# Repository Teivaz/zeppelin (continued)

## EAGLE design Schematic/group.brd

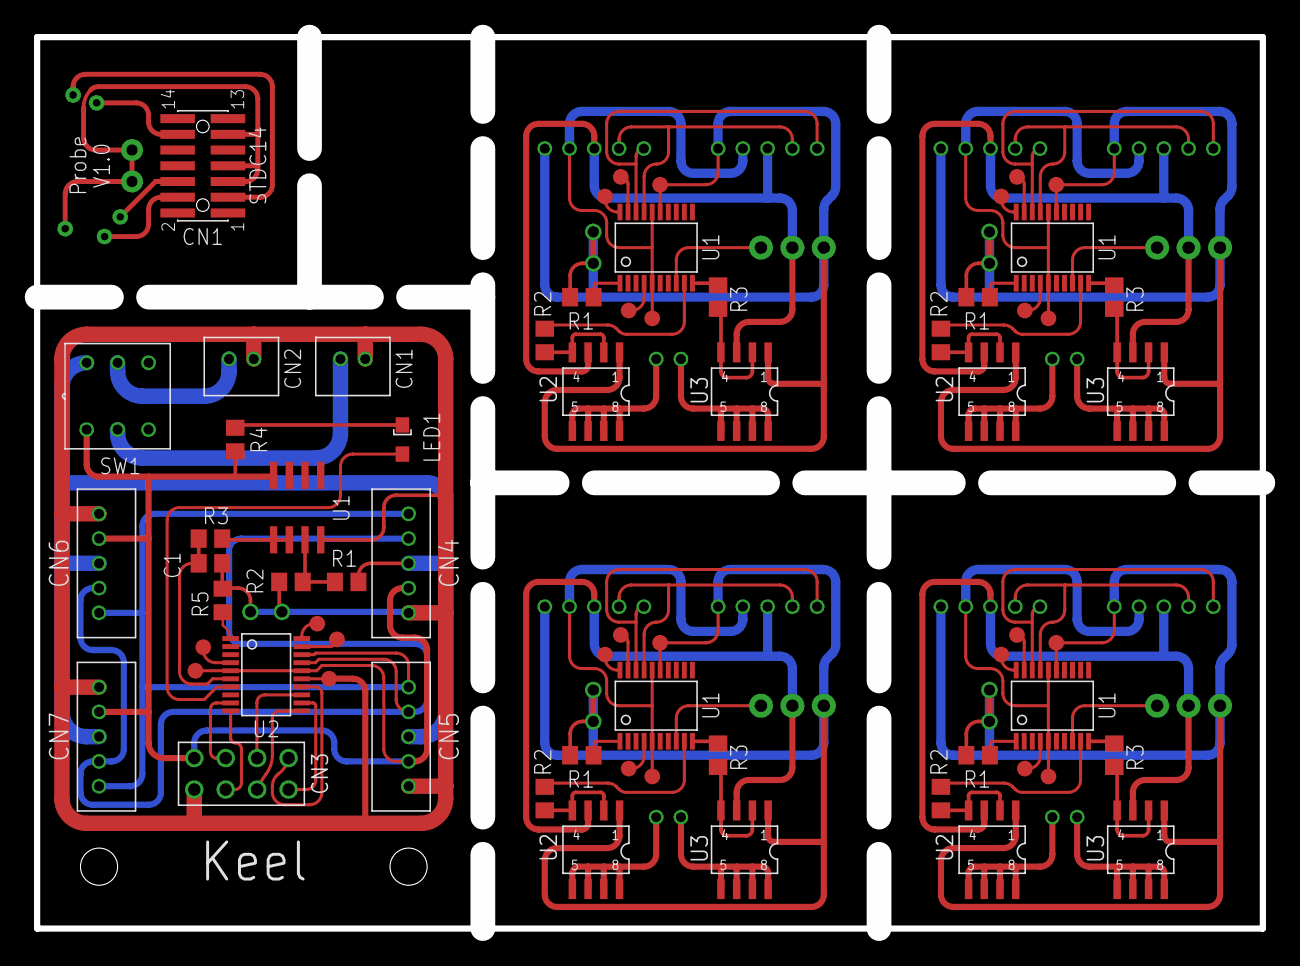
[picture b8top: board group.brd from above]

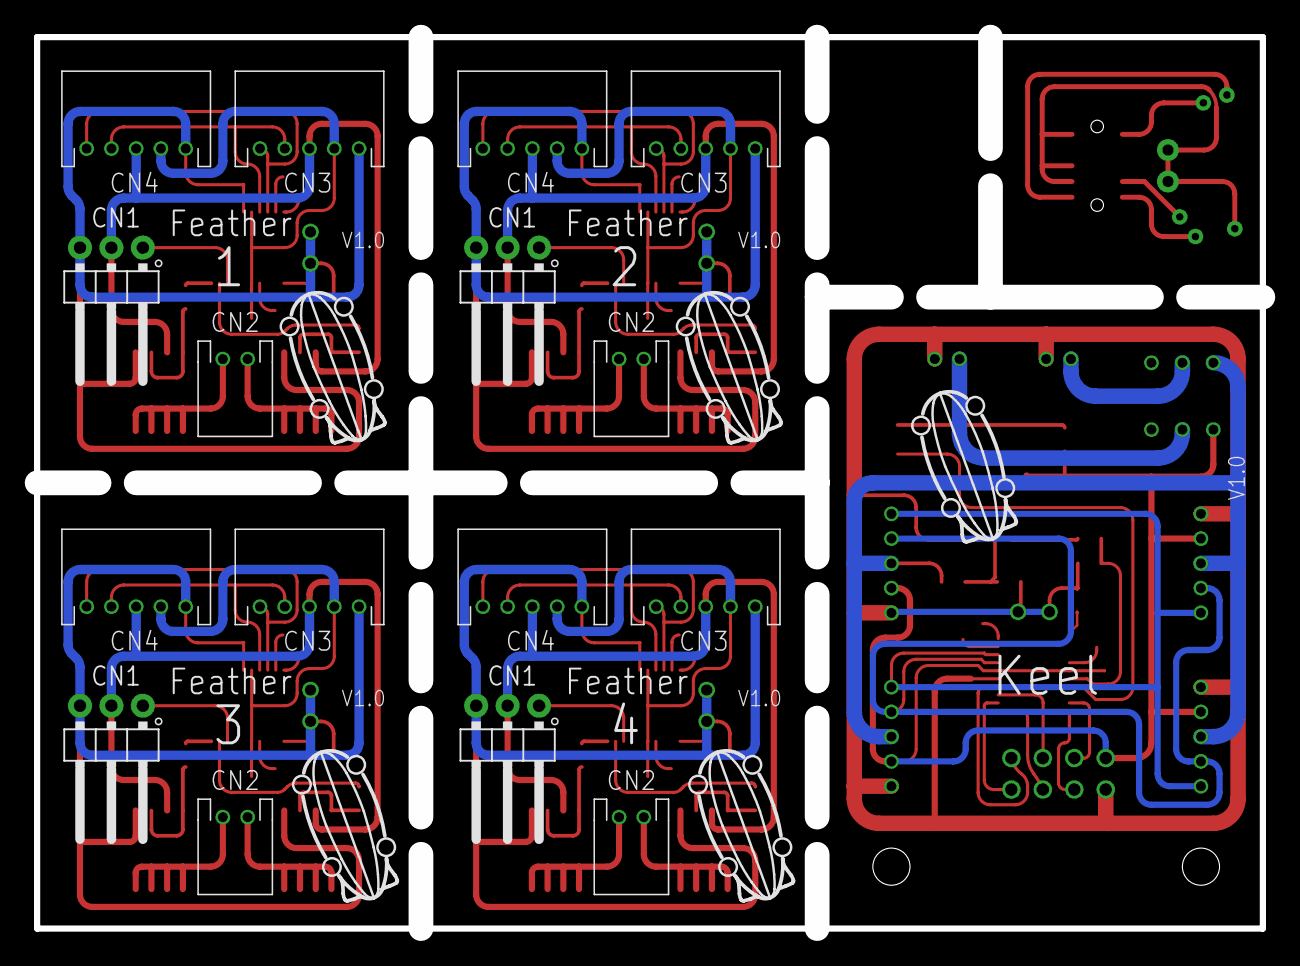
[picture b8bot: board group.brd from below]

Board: 2 copper layers, 99.0 x 72.0 mm, 69 parts (21 on the bottom side), 91 nets.

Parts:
C1: 470pf; C0805
CN0, CN10, CN15, CN20, CN25: KEEL_PROBE1IC; KEEL_PROBE-IC1
CN1: STDC14; FTSH-107-01-L-DV-K-A
CN2: KEEL_PROBE1PROBE; KEEL_PROBE1
CN3: BAT0; 1X2
CN4: BAT1; 1X2
CN5: NRF24013; PIN
CN6: F1; 1X5
CN7: F2; 1X5
CN8: F3; 1X5
CN9: F4; 1X5
CN11, CN16, CN21, CN26: 1X2HORIZONTAL; 1X2H
CN12, CN14, CN17, CN19, CN22, CN24, CN27, CN29: F1; 1X5H
CN13, CN18, CN23, CN28: 1X03/90
E$1, E$2, E$3, E$4, E$5: ZEPPELIN
LED1: AP2012
R1, R2: 10k; R0805
R3: 500r; R0805
R4: 300r; R0805
R5, R8, R11, R14, R17: 1k; R0805
R6, R7, R9, R10, R12, R13, R15, R16: 51k; R0805
SW1: TL2201
U1: LM358D; SO08
U2, U5, U8, U11, U14: STM32L011; SSOP20
U3, U4, U6, U7, U9, U10, U12, U13: IRF7105; SO8-2

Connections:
+3V1: CN12.3, CN13.2, CN14.3, U3.3, U4.3
+3V2: CN17.3, CN18.2, CN19.3, U6.3, U7.3
+3V3: CN6.3, CN7.3, CN8.3, CN9.3, R1.2, SW1.4
+3V4: CN22.3, CN23.2, CN24.3, U9.3, U10.3
+3V5: CN27.3, CN28.2, CN29.3, U12.3, U13.3
GND: CN1.05, CN1.07, CN1.11, CN2.GND, CN2.GND-D1, CN2.GND-D2
GND1: C1.1, CN0.GND, CN0.GND-D1, CN0.GND-D2, CN3.2, CN4.2, CN5.1, CN6.1, CN7.1, CN8.1, CN9.1, R2.1, R5.1, U1.4, U2.15
GND2: CN10.GND, CN10.GND-D1, CN10.GND-D2, CN12.1, CN13.3, CN14.1, R8.1, U3.1, U4.1, U5.15
GND3: CN15.GND, CN15.GND-D1, CN15.GND-D2, CN17.1, CN18.3, CN19.1, R11.1, U6.1, U7.1, U8.15
GND4: CN20.GND, CN20.GND-D1, CN20.GND-D2, CN22.1, CN23.3, CN24.1, R14.1, U9.1, U10.1, U11.15
GND5: CN25.GND, CN25.GND-D1, CN25.GND-D2, CN27.1, CN28.3, CN29.1, R17.1, U12.1, U13.1, U14.15
I2C_SCL: CN6.4, CN7.4, CN8.4, CN9.4, U2.17
I2C_SCL1: CN12.4, CN14.4, U5.17
I2C_SCL2: CN17.4, CN19.4, U8.17
I2C_SCL3: CN22.4, CN24.4, U11.17
I2C_SCL4: CN27.4, CN29.4, U14.17
I2C_SDA: CN6.5, CN7.5, CN8.5, CN9.5, U2.18
I2C_SDA1: CN12.5, CN14.5, U5.18
I2C_SDA2: CN17.5, CN19.5, U8.18
I2C_SDA3: CN22.5, CN24.5, U11.18
I2C_SDA4: CN27.5, CN29.5, U14.18
unnamed: R1.1, R2.2, U1.3
unnamed: LED1.C, R4.2
unnamed: LED1.A, U2.7
unnamed: C1.2, R3.1, U2.6
unnamed: R5.2, U2.1
unnamed: R3.2, U1.1, U1.2
unnamed: CN4.1, SW1.5
unnamed: CN3.1, SW1.2
unnamed: CN11.2, U3.5, U3.6, U3.7, U3.8
unnamed: CN11.1, U4.5, U4.6, U4.7, U4.8
unnamed: R6.1, U3.2, U3.4
unnamed: R7.2, U4.2, U4.4
unnamed: R8.2, U5.1
unnamed: R7.1, U5.10
unnamed: R6.2, U5.9
unnamed: CN13.1, U5.8
unnamed: CN16.2, U6.5, U6.6, U6.7, U6.8
unnamed: CN16.1, U7.5, U7.6, U7.7, U7.8
unnamed: R9.1, U6.2, U6.4
unnamed: R10.2, U7.2, U7.4
unnamed: R11.2, U8.1
unnamed: R10.1, U8.10
unnamed: R9.2, U8.9
unnamed: CN18.1, U8.8
unnamed: CN21.2, U9.5, U9.6, U9.7, U9.8
unnamed: CN21.1, U10.5, U10.6, U10.7, U10.8
unnamed: R12.1, U9.2, U9.4
unnamed: R13.2, U10.2, U10.4
unnamed: R14.2, U11.1
unnamed: R13.1, U11.10
unnamed: R12.2, U11.9
unnamed: CN23.1, U11.8
unnamed: CN26.2, U12.5, U12.6, U12.7, U12.8
unnamed: CN26.1, U13.5, U13.6, U13.7, U13.8
unnamed: R15.1, U12.2, U12.4
unnamed: R16.2, U13.2, U13.4
unnamed: R17.2, U14.1
unnamed: R16.1, U14.10
unnamed: R15.2, U14.9
unnamed: CN28.1, U14.8
NRST: CN1.12, CN2.NRST
NRST1: CN0.NRST, U2.4
NRST2: CN10.NRST, U5.4
NRST3: CN15.NRST, U8.4
NRST4: CN20.NRST, U11.4
NRST5: CN25.NRST, U14.4
SPI_CE: CN5.3, U2.10
SPI_CSN: CN5.4, U2.9
SPI_IRQ: CN5.8, U2.14
SPI_MISO: CN5.7, U2.12
SPI_MOSI: CN5.6, U2.13
SPI_SCK: CN5.5, U2.11
SWCLK: CN1.06, CN2.CLK
SWCLK1: CN0.CLK, U2.20
SWCLK2: CN10.CLK, U5.20
SWCLK3: CN15.CLK, U8.20
SWCLK4: CN20.CLK, U11.20
SWCLK5: CN25.CLK, U14.20
SWDIO: CN1.04, CN2.DIO
SWDIO1: CN0.DIO, U2.19
SWDIO2: CN10.DIO, U5.19
SWDIO3: CN15.DIO, U8.19
SWDIO4: CN20.DIO, U11.19
SWDIO5: CN25.DIO, U14.19
T_VCC: CN1.03, CN2.VCC
VCC: CN0.VCC, CN5.2, CN6.2, CN7.2, CN8.2, CN9.2, R4.1, SW1.1, U1.8, U2.5, U2.16
VCC1: CN10.VCC, CN12.2, CN14.2, U5.5, U5.16
VCC2: CN15.VCC, CN17.2, CN19.2, U8.5, U8.16
VCC3: CN20.VCC, CN22.2, CN24.2, U11.5, U11.16
VCC4: CN25.VCC, CN27.2, CN29.2, U14.5, U14.16

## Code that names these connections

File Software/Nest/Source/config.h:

#ifndef _CONFIG_H_
#define _CONFIG_H_

#define CLK		PB7 // Will be driven via hardware
#define CSN		PB4	// do not change
#define MOSI	PB5 // Will be driven via hardware
#define INT		PB3 // Do we need this?
#define DBG		PB3

#define STREAM_BUFFER_SIZE  64

#define QUERY_PERIOD 50	// time in ms

#define PORTA_ 0x1B
#define PORTB_ 0x18
#define PORTC_ 0x15
#define PORTD_ 0x12

//						    F-L-S	F-L-M	B-R-S	B-R-M
#define STICK_BTN_PORTS    {PORTB_,	PORTB_,	PORTB_,	PORTB_}
#define STICK_BTN_PINS     {PB0,	PB1,	PB2,	PB3}
#define STICK_ADC_PORTS	   {0, 1,	2, 3,	4, 5,	6, 7}
	
#define STICK_FLM_LED_PORT PORTB
#define STICK_FLM_LED_PIN  PB1
#define STICK_FLS_LED_PORT PORTB
#define STICK_FLS_LED_PIN  PB1
#define STICK_BRM_LED_PORT PORTB
#define STICK_BRM_LED_PIN  PB1
#define STICK_BRS_LED_PORT PORTB
#define STICK_BRS_LED_PIN  PB1

#define MODE_LED_PORT	PORTB
#define MODE_LED_PIN	PB1
#define MODE_BTN_PORT	PORTB
#define MODE_BTN_PIN	PB1

#define CAL_BTN_TIME	50
#define CAL_BTN_PORT	PORTB
#define CAL_BTN_PIN		PB1
#define CAL_LED_PORT	PORTB
#define CAL_LED_PIN		PB1


#endif //_CONFIG_H_

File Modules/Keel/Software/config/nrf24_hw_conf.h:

#pragma once

#include "stm32l0xx_hal.h"

// Hardware abstraction layer for NRF24L01+ transceiver (hardware depended functions)
// GPIO pins definition
// GPIO pins initialization and control functions
// SPI transmit functions

// SPI port peripheral
#define NRF24_SPI_PORT             SPI1

// CE (chip enable) pin (PA4)
#define NRF24_CE_PORT              GPIOA
#define NRF24_CE_PIN               GPIO_PIN_4

// CSN (chip select negative) pin (PA3)
#define NRF24_CSN_PORT             GPIOA
#define NRF24_CSN_PIN              GPIO_PIN_3

// IRQ pin (PB2)
#define NRF24_IRQ_PORT             GPIOB
#define NRF24_IRQ_PIN              GPIO_PIN_1

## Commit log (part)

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2013-08-10 Initial commit of all I have
2013-08-10 Added software part
2013-08-10 Added missing files
2013-08-10 Update ignore file
2013-08-11 Added schematics and circuits empty projects
2013-08-11 Removed old project
2013-08-11 Added new projects for client and server sides
2013-08-11 simple servo driver for attiny13
2013-08-11 Modified simple servo driver for attiny13
2013-08-12 Added device datasheets
2013-08-12 Added more datasheets
2013-08-14 Added schematics lib for transistor pair irf7105 Added schematics for H-bridge
2013-08-15 Updated code for DC motor control
2013-08-15 Updated libs for Nest project
2013-08-15 Renamed main file
2013-08-15 Updated list to buy
2013-08-15 Added readme for Keel project Updated source for Keel project
2013-08-15 Updated Keel source
2013-08-16 Added config and utils for Keel
2013-08-16 Added defines file for transceiver
2013-08-16 Refactored project file structure
2013-08-16 Added transmit pool Updated code for Keel Dendrite module
2013-08-16 Fixed stream buffer. Now it works, but still needs a fix. Configured Keel timer. Modified Keel Axon.
2013-08-16 Fixed Feather SPI receiver
2013-08-16 Removed Feather stm32 source and projects
2013-08-16 Refactored file structure in Feather project Removed stm32 Feather projects Added SystemConfig.h and ModuleConfig.h Updated DC motor controller
2013-08-16 Fixed stream initialization
2013-08-16 Added Keel adc control for testing
2013-08-19 Added EEPROM memory for attiny25 with letters "Z1"
2013-08-19 Modified Feather code. Now primary and secondary letters are stored in EEPROM
2013-08-19 Added schematics for Feather
2013-08-19 Feather board routed
2013-08-19 Rounded corners to look nice and pass DRC
2013-08-19 Added code drafts for servo Feather
2013-08-19 Created EEPROM memory for the rest of feathers
2013-08-24 Moved servo and dc motor from dirajuble
2013-08-24 Scaled ballon
2013-08-24 Set balloon scale
2013-08-24 Added flaps
2013-08-24 more flaps added layout and dimensions
2013-08-25 Changed mcu, redrawn scheme, redrawn pcb
2013-08-25 Created PCB for Keel
2013-08-25 Simplify PCB by remapping pins
2013-08-25 Updated PCB
2013-08-25 Added CRC check Removed old reference
2013-08-25 Added new references
2013-08-25 Added CRC to Keel project
2013-08-25 updated todo lists
2013-08-25 More lib references for Nest
2013-08-25 Added Feather blueprints
2013-08-25 Added more details
2013-08-25 Added separate file for Feather motor cover
2013-08-26 Converted to curves
2013-08-26 More curves
2013-08-26 Created surface
2013-08-26 Prolonged servo cover
2013-08-26 Added renders
2013-08-26 Added assembled balloon
2013-08-26 Added rendered video for assembled zeppelin flight
2013-08-26 Added 3dMax project for assembled zeppelin flight
2013-08-27 Added stabilizer reference
2013-08-27 Updated wrap for balloon 4.4[m] x 1.2[m] and 3[m] x 1.5[m]
2013-08-29 Fixed SPI word size
2013-08-29 Configured Keel for Feather tests
2013-08-30 Added servo configurations Fixed servo pins Added servo controller Cleaned up unused code
2013-08-30 Moved out files to corresponding category Created Feather firmware for ATTiny25
2013-08-30 Removed unnecessary function call in Feather project Regenerated Feather firmware
2013-08-30 Split CPU power and motor power Updated PCB
2013-08-30 Updated software implementation status
2013-08-30 Updated to buy list
2013-08-30 Updated Keel communication with transceiver Fixed TransmitPool
2013-08-30 Removed old Nest project for STM32 Created new Nest project for ATMega16
2013-09-04 Changed project from CPP to C. Added main logic to Nest Dendrite module
2013-09-04 Updated wrap
2013-09-05 Added Nest eeprom savable data Updated Nest Dendrite source
2013-09-05 Updated SystemConfig.h for storing letters in flash or EEPROM Added Axon source to project Nest Added configuration for hardware Created Transmission functions
2013-09-05 Fixed compilation errors Added test project
2013-09-05 Updated Test.c Removed some errors Added initialization
2013-09-05 More errors fixed
2013-09-06 More configurations added Added Feather calibration mode
2013-09-06 Added min max Updated stick calibration mode
2013-09-06 Added Nest prototype
2013-09-06 Updated abs function Added defines to Nest.cproj Updated buttons processing Added led indicator processing
2013-09-06 Fixed multiple stick calibration
2013-09-07 Added Nest mode icons variants
2013-09-08 Added project icon Added stickers with icon
2013-09-08 Added project icon
2013-09-12 Added 3draft added 3draft renders added stck model added icon renders
2013-09-12 minor declaration
2013-09-12 updated print
2013-09-12 Added ready for print
2013-09-12 Added stick references Added Nest pcb dimensions Added 3draft of smaller size
2013-09-13 Added stick footprint Drawn Nest PCB dimensions Added sticks on board and scheme
2013-09-14 Added outfiles for printing Feather and Keel PCBs
2013-09-14 Added composite file for Keel and Feather PCBs
2013-09-14 Refactoring of Axon module in Nest proj. Added configuration functions for Nest
2013-09-14 Changed Nest SPI mode to synchronous
2013-09-15 Removed unused files Changed Keel SPI mode to synchronous
2013-09-15 Nest. Fixed data sending via Axon Nest. Fixed EEPROM data loading
2013-09-16 Changed gray color to black on blueprints
2013-09-17 added balloon segment dimensions.png
2013-09-18 Added PVC film info
2013-09-18 IT WORKS WITH THIS!
2013-09-18 Compiled Feather firmware in release configuration. Need to check timings.
2013-09-18 Cleaned up Keel proj Compiled Keel in release Added Keel firmware
2013-09-18 Changed Nest query time to 50 ms Updated transmitter configuration
2013-09-20 Updated outfiles for increased pads size
2013-09-20 Nest scheme. Added RF module. Routed bottom layer with ground and power buses
2013-09-21 Added connector project for firmware uploading
2013-09-21 saved connector schematics project
2013-09-22 Keel scheme. Routed PCB for fixed circuit Nest scheme. Added elements and routed a piece of PCB
2013-09-26 Added new blueprint for 3draft with full scale Renamed old files to fix mistakes
2014-03-19 Feather. Removed old interrupt on SPI clock
2014-03-19 Feather. Refactored package processing
2014-08-15 - Updated calculations
2014-08-15 * Correctly merged
2014-08-15 - [Feather] Optimized package reading. Implemented time reset.
2014-08-15 - [Feather] added package dead time function call
2014-08-15 - minor improvements
2014-08-16 -! [Feather] Package processing refactored
2014-08-16 + Added scripts for firmware uploading to atmega16 * Fixed Nest release configuration
2014-08-19 * Fixed feather bugs - Feather debugging functions added ! Not working feather - Updated upload scripts - Updated calculations for selected fabrics
2014-08-20 - [Keel] General cleanup for keel sources
2014-08-21 - [Feather] Updated script and fixed USI byte overflow
2014-08-21 * Fixed Feather - Removed debug calls
2014-08-21 + Added scripts for uploading firmware + Added faster CRC - Updated firmwares for keel and feather
2014-08-21 - Updated Keel PCB
2014-09-08 + Added attiny2313a datasheet
2014-09-11 - Basics of soft spi
2016-06-11 Added mounts for feather components. Added feather models for printing. Refactored feather software.
2016-06-11 Translated calculations
2016-06-12 Updated CRC function (now using xor). Created Buffer class for feather. Refactored message processing.
2016-06-13 Changed type to basic in utils.h. Minor refactoring of Keel. Removed SoftSpi library. Updated project for Keel.
2016-06-18 Update Keel config for new MCU type (attiny2313)
2016-06-19 Software. Fixed asm nop macro. Keel removed unused code, updated config and logic for new controller attiny2313
2016-06-19 Ignored temporary and generated files. Keel Software. Removed redundant files of SPI module. Cleaned up code and fixed bugs.
2016-06-19 Keel software. Added generated and tested hex
2016-07-14 Updated dimension of the motor GPS-7
2016-07-14 Bluetooth datasheet
2016-08-03 Added 3d models for parts
2016-09-01 updated icons. Now symmetric
2019-12-27 Added new parts' data sheets
2020-01-05 Added protocol Added readme for the beacon project
2020-01-05 Added software project for the Beacon
2020-01-05 Removed extra command
2020-01-05 Added CRC calculation
2020-01-05 Addeed beacon schematics
2020-01-08 Added motor details
2020-01-16 Added part of cmake project for the new MCU
2020-01-16 Added HAL and CMSIS libraries
2020-01-16 Moved config outside of sources
2020-01-18 Added other sections to the linker script
2020-01-18 Added weak interrupt handlers
2020-01-18 Added RTC setup
2020-01-18 Cleaned up the system file
2020-01-18 Zero intializing bss section
2020-01-18 Enabled external interrupts
2020-01-18 Enabled Os optimization Added code to send data Fixed nrf24 lib printing
2020-01-18 Added project for the Keel
2020-01-18 Changed Keel code to receiver
2020-01-18 Fixed SPI intialization code. Working transmitter and receiver
2020-01-19 Added eeprom memory
2020-01-19 Const interface for protocol Added more endpoint data for protocol
2020-01-19 Fixed eeprom hex generation
2020-01-20 Fixed cmake command
2020-01-20 Updated api of protocol lib
2020-01-20 Now beacon module is using terminal and protocol libs
2020-01-20 Enabled dynamic payload length
2020-01-20 Writing to eeprom
2020-01-20 Added more commands
2020-01-24 Added I2C configuration Added code for Feather module
2020-01-25 Added PZ_needsResponse function
2020-01-25 Added missing functions to feather CV and DV
2020-01-25 Added Keel CV and DV
2020-01-26 Added const
2020-01-26 Fixed serialization
2020-01-27 Fixed protocol data serialization
2020-01-27 Fixed protocol lib
2020-01-27 [Beacon] Updated cmake lists Moved spi processing to main thread polling
2020-01-27 [Feather] Disabled UART Updated cmake Removed printf dependency Changed include guards Added working I2C communication setup
2020-01-27 [Keel] Disabled UART Added working I2C master setup Removed old files Updated cmake
2020-01-28 Updated protocol with information about units
2020-01-28 [Keel] Enabled voltage and temperature measuring
2020-01-28 Updated ADC sample time
2020-01-28 [Keel] Added battery1 measuring
2020-01-29 Moved eagle libraries and project
2020-01-29 Updated ignore
2020-01-29 Updated transmit speed Improved bat1 measuring prescision
2020-01-29 Updated DRU
2020-01-31 Added libraries for used components
2020-01-31 Traced keel
2020-01-31 Traced probe
2020-01-31 Added more eagle files to ignore
2020-02-01 Added zeppelin logo eagle library
2020-02-01 Updated libraries Added DRU Added group board variants
2020-02-03 Updated milling and border layers
2020-02-03 downgraded version eagle version to 9.2.2
2020-02-06 Enabled timer21 for servo drive
2020-02-06 Parsing hex strings instead
2020-02-07 [Feather] Added servo calibration mode Updated protocol documentation Fixed I2C address change
2020-02-07 [Keel] Fixed inifnite loop on I2C error
2020-02-08 Extracted servo code to a separate fileAdded motor controller codeUpdated motor calibration documentation
2020-02-08 Added calibration mode for the motor
2020-02-08 Removed RTC and other redundant code from feather
2020-02-08 Removed old circuits and schematics
2020-02-08 Added notes
2020-02-11 WIP Updated nRF24 lib according to datasheet Added HAL-like interface for nRF24
2020-02-11 ignored temp file
2020-02-11 Added frequency parameter to flash tasks
2020-02-11 Added datasheet for nRF24L01+Removed old datasheet
2020-02-11 Moved Beacon module one folder up
2020-02-11 Moved Feather module one folder up
2020-02-11 Ignored temporary files
2020-02-15 Fixed nrf24 library
2020-02-15 Fixed initialization of nrf24 Set speed to 2Mbps Added commands for beacon
2020-02-16 Fixed pinhead numbering
2020-02-16 Fixed schematic issues from version 1.0.0 Added datasheets for new components
2020-02-16 Replaced regulator with LDO
2020-02-17 Added code for stm32wb55 nucleo board
2020-02-18 Added HAL library for stm32wb
2020-02-18 Moved template files outside the HAL driver
2020-02-18 Added config file
2020-02-27 Updated CMSIS to v5.0.4
2020-02-27 Fixed boot file
2020-02-27 Added heap
2020-02-27 Added trash code generated by Cube MX
2020-02-27 Reimplemented interrupts handler
2020-02-27 Reimplemented msp
2020-02-27 Reimplemented wpan application init
2020-02-27 Replaced app ble with bleapp
2020-02-27 Fixed warnings
